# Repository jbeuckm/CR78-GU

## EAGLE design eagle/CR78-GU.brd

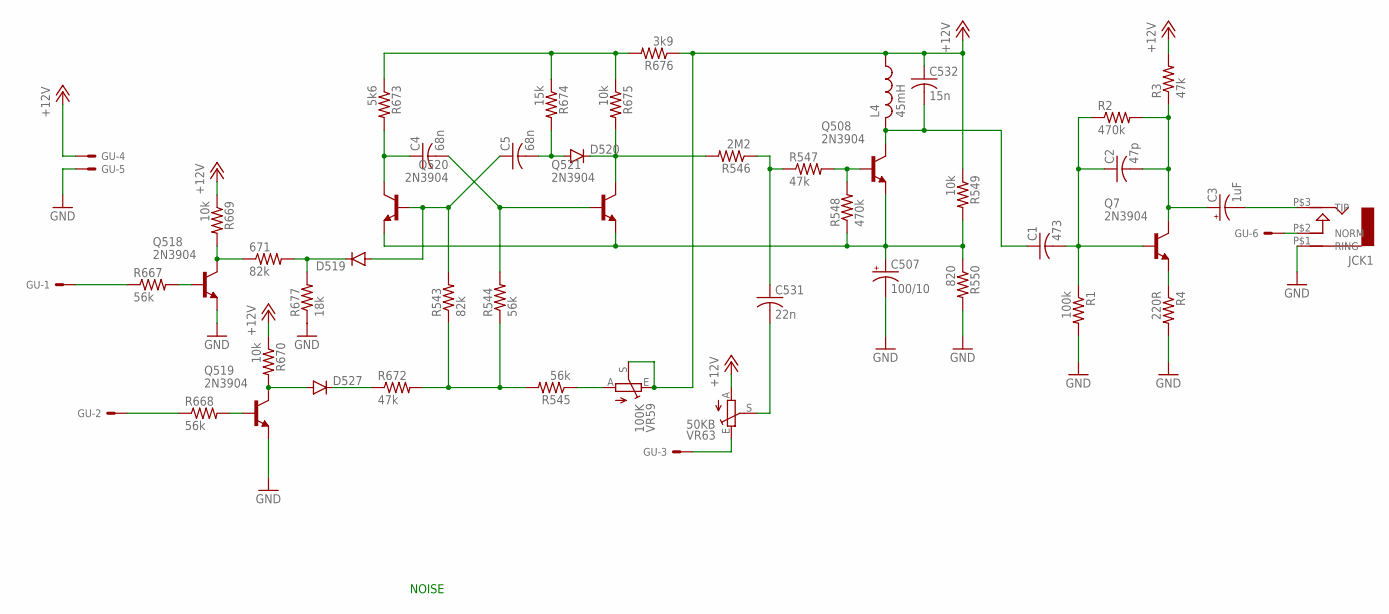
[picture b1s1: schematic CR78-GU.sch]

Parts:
671: 82k; 0207/7
C1: 473; C050-025X075
C2: 47p; C050-025X075
C3: 1uF; B45181A
C4, C5: 68n; C050-025X075
C507: 100/10; B45181A
C531: 22n; C050-025X075
C532: 15n; C050-025X075
D519, D520, D527: DIODE1N4148; DIODE-1N4148
GU: 22-23-2061
JCK1: AUDIO-JACK; ERTHENVAR-JACK-90DEG
L4: 45mH; 0204/7
Q7, Q508, Q518, Q519, Q520, Q521: 2N3904; TO92
R1: 100k; 0207/7
R2, R548: 470k; 0207/7
R3, R547, R672: 47k; 0207/7
R4: 220R; 0207/7
R543: 82k; 0207/7
R544, R545, R667, R668: 56k; 0207/7
R546: 2M2; 0207/7
R549, R669, R670, R675: 10k; 0207/7
R550: 820; 0207/7
R673: 5k6; 0207/7
R674: 15k; 0207/7
R676: 3k9; 0207/7
R677: 18k; 0207/7
VR59: 100K; B64Y
VR63: 50KB; B64Y

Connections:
+12V: C532.1, GU.4, L4.1, R3.2, R549.1, R669.1, R670.1, R676.1, VR59.E, VR59.S, VR63.A
GND: C507.-, GU.5, JCK1.P$1 (RING), Q518.3 (E), Q519.3 (E), R1.2, R4.2, R550.2, R677.1
unnamed: 671.2, D519.C, R677.2
unnamed: C5.1, D519.A, Q520.2 (B), R543.2
unnamed: GU.3, VR63.E
unnamed: C507.+, Q508.3 (E), Q520.3 (E), Q521.3 (E), R548.1, R549.2, R550.1
unnamed: D520.C, Q521.1 (C), R546.2, R675.2
unnamed: C5.2, D520.A, R674.2
unnamed: GU.6, JCK1.P$2 (NORM)
unnamed: C4.2, Q521.2 (B), R544.2
unnamed: C4.1, Q520.1 (C), R673.2
unnamed: R673.1, R674.1, R675.1, R676.2
unnamed: GU.2, R668.1
unnamed: C531.1, R546.1, R547.1
unnamed: Q508.2 (B), R547.2, R548.2
unnamed: R545.1, VR59.A
unnamed: Q7.3 (E), R4.1
unnamed: C2.2, C3.+, Q7.1 (C), R2.2, R3.1
unnamed: C531.2, VR63.S
unnamed: C1.2, C2.1, Q7.2 (B), R1.1, R2.1
unnamed: C3.-, JCK1.P$3 (TIP)
unnamed: 671.1, Q518.1 (C), R669.2
unnamed: Q518.2 (B), R667.2
unnamed: R543.1, R544.1, R545.2, R672.2
unnamed: D527.C, R672.1
unnamed: GU.1, R667.1
unnamed: C1.1, C532.2, L4.2, Q508.1 (C)
unnamed: D527.A, Q519.1 (C), R670.2
unnamed: Q519.2 (B), R668.2

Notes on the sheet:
NOISE

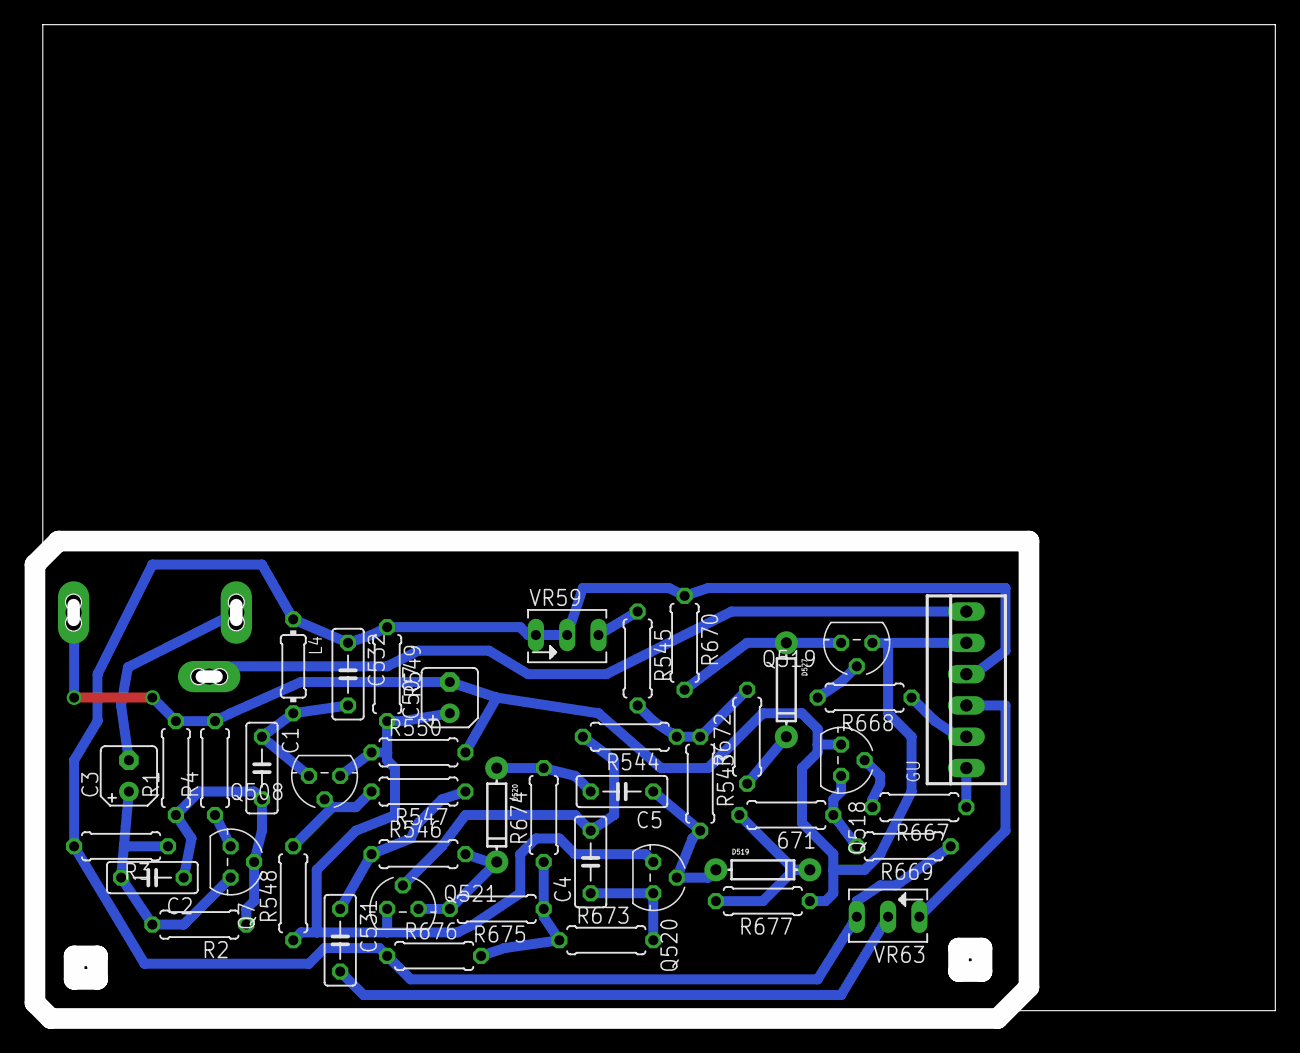
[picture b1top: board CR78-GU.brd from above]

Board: 2 copper layers, 100.6 x 80.6 mm, 45 parts (0 on the bottom side), 29 nets.

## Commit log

2016-06-14 transitioning from tb
2016-06-14 connector for gu
2016-06-15 more schemo
2016-06-15 schemo in
2016-06-16 fixed noise input and started board
2016-06-16 parts on board
2016-06-16 routed with cutout

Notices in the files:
parts and their libraries:
SparkFun-DiscreteSemi: Licensing: Creative Commons ShareAlike 4.0 International - https://creativecommons.org/licenses/by-sa/4.0
